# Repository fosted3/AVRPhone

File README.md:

AVRPhone
========

AVRPhone is an attempt to simplify and condense classic phone functionality while keeping modern security and openness in mind. The project aims to use a combination of easily accessible off-the-shelf hardware and clear and modular open source software in pursuit of this goal.

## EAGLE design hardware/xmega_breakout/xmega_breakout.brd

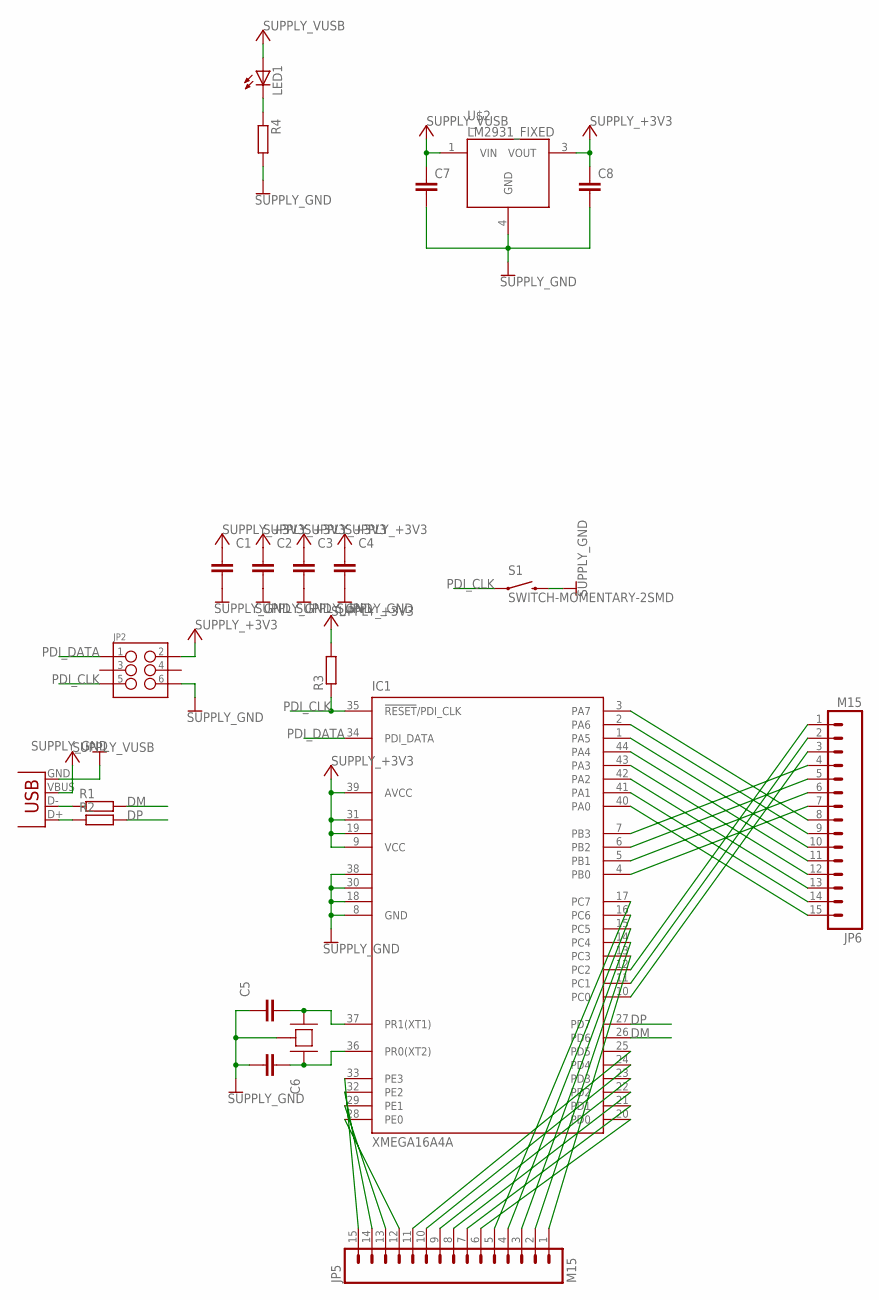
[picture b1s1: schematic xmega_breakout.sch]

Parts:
C1, C2, C3, C4, C5, C6: CAPACITOR_NPOL-0402; C402
C7, C8: C-EUC1210; C1210
IC1: XMEGA16A4A; TQFP44
JP1: USBSMD; USB-MINIB
JP2: M03X22X3_SILK_SM; 2X3
JP5, JP6: M15; 1X15
LED1: LED-0603; LED-603
R1, R2, R3: RESISTOR-0402; R402
R4: RESISTOR-0603; R603
S1: SWITCH-MOMENTARY-2SMD; TACTILE_SWITCH_SMD
U$1: CRYSTAL-3.2X2.5; TSX-3225
U$2: LM2931_FIXED; DPAK

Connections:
+3V3: C1.1, C2.1, C3.1, C4.1, C8.1, IC1.9 (VCC), IC1.19 (VCC1), IC1.31 (VCC2), IC1.39 (AVCC), JP2.2, R3.2, U$2.3 (VOUT)
DM: IC1.26 (PD6), R1.2
DP: IC1.27 (PD7), R2.2
GND: C1.2, C2.2, C3.2, C4.2, C5.1, C6.2, C7.2, C8.2, IC1.8 (GND), IC1.18 (GND1), IC1.30 (GND2), IC1.38 (GND3), JP1.GND, JP2.6, R4.2, S1.3 (2), U$1.G1 (GND), U$1.G2 (GND), U$2.4 (GND)
unnamed: C5.2, IC1.37 (PR1(XT1)), U$1.C1
unnamed: C6.1, IC1.36 (PR0(XT2)), U$1.C2
unnamed: JP1.D-, R1.1
unnamed: JP1.D+, R2.1
unnamed: IC1.33 (PE3), JP5.15
unnamed: IC1.32 (PE2), JP5.14
unnamed: IC1.29 (PE1), JP5.13
unnamed: IC1.28 (PE0), JP5.12
unnamed: IC1.25 (PD5), JP5.11
unnamed: IC1.24 (PD4), JP5.10
unnamed: IC1.23 (PD3), JP5.9
unnamed: IC1.22 (PD2), JP5.8
unnamed: IC1.21 (PD1), JP5.7
unnamed: IC1.20 (PD0), JP5.6
unnamed: IC1.17 (PC7), JP5.5
unnamed: IC1.16 (PC6), JP5.4
unnamed: IC1.15 (PC5), JP5.3
unnamed: IC1.14 (PC4), JP5.2
unnamed: IC1.13 (PC3), JP5.1
unnamed: IC1.12 (PC2), JP6.1
unnamed: IC1.11 (PC1), JP6.2
unnamed: IC1.10 (PC0), JP6.3
unnamed: IC1.7 (PB3), JP6.4
unnamed: IC1.6 (PB2), JP6.5
unnamed: IC1.5 (PB1), JP6.6
unnamed: IC1.4 (PB0), JP6.7
unnamed: IC1.3 (PA7), JP6.8
unnamed: IC1.2 (PA6), JP6.9
unnamed: IC1.1 (PA5), JP6.10
unnamed: IC1.44 (PA4), JP6.11
unnamed: IC1.43 (PA3), JP6.12
unnamed: IC1.42 (PA2), JP6.13
unnamed: IC1.41 (PA1), JP6.14
unnamed: IC1.40 (PA0), JP6.15
unnamed: LED1.C, R4.1
PDI_CLK: IC1.35 (!RESET!/PDI_CLK), JP2.5, R3.1, S1.1
PDI_DATA: IC1.34 (PDI_DATA), JP2.1
VUSB: C7.1, JP1.VBUS, LED1.A, U$2.1 (VIN)

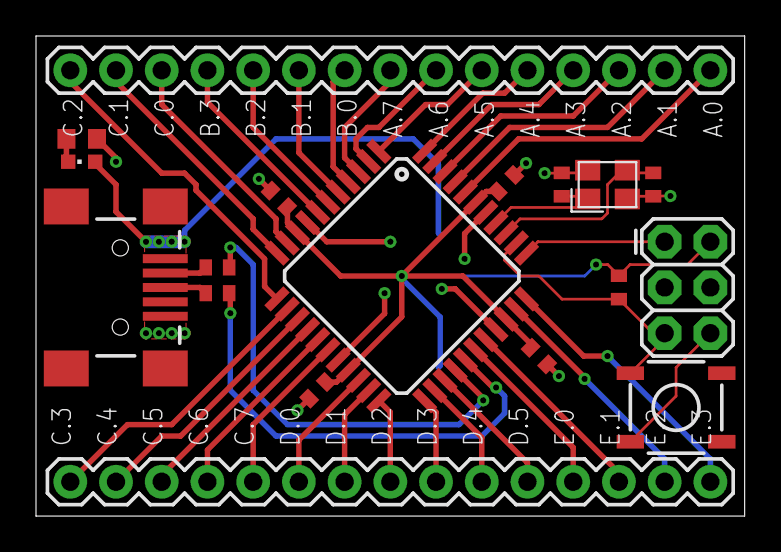
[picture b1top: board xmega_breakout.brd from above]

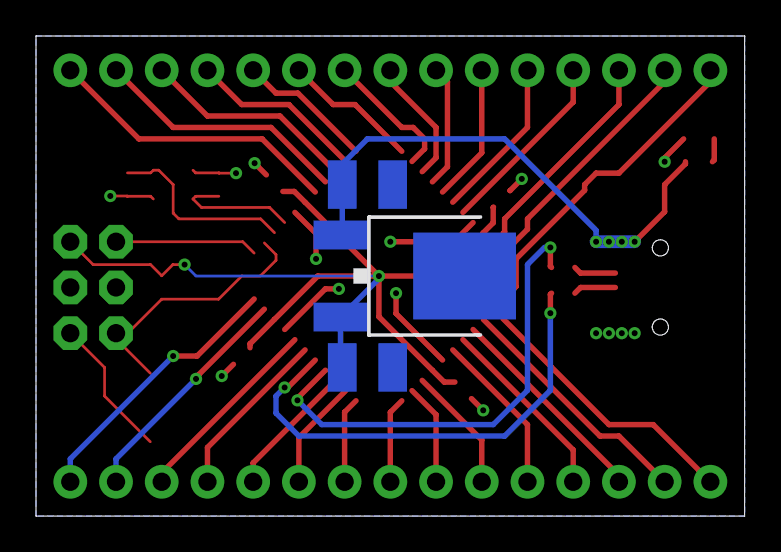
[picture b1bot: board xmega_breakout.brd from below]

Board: 2 copper layers, 39.4 x 26.7 mm, 21 parts (3 on the bottom side), 42 nets.

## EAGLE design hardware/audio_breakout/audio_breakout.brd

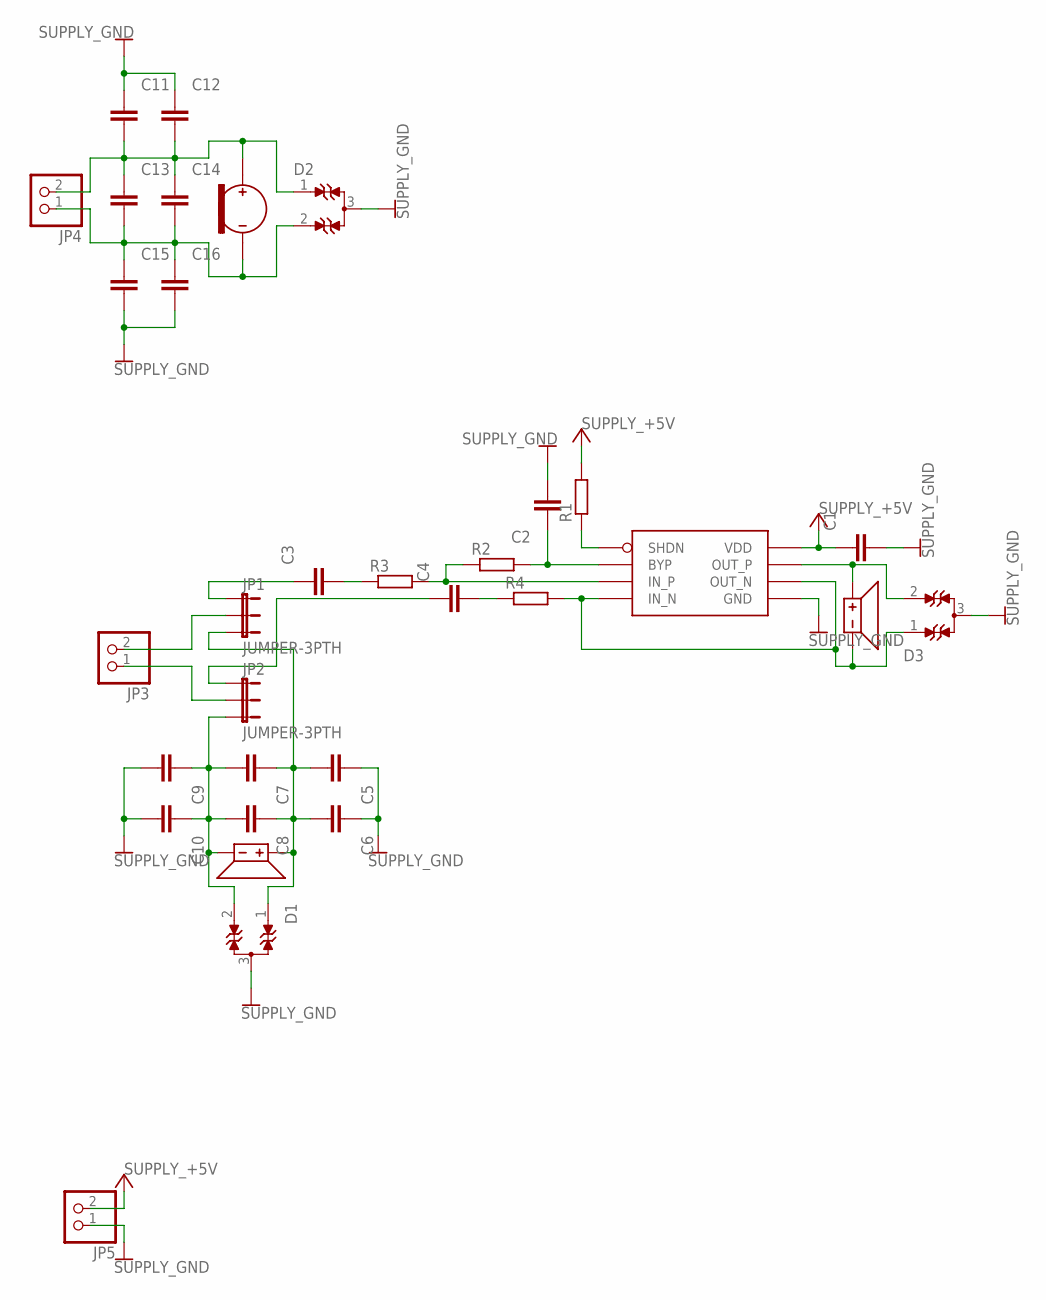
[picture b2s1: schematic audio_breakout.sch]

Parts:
C1, C2, C3, C4, C5, C6, C7, C8, C9, C10, C11, C12, C13, C14, C15, C16: CAPACITOR_NPOL-0603; C603
D1, D2, D3: WE-TVS_824022; WE-TVS_SOT23-3L
JP1, JP2: JUMPER-3PTH; 1X03
JP3, JP4, JP5: PINHD-1X2; 1X02
R1, R2, R3, R4: RESISTOR-0603; R603
U$1: LM4890; SOIC-8-NARROW
U$2: SPEAKER-2403-260-00001; 2403-260-00001
U$3: SPEAKER-2403-260-00031; 2403-260-00031
U$4: MIC-ELECTRET-9.7MM; 9.7MM-ELECTRET

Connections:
+5V: C1.1, JP5.2, R1.2, U$1.6 (VDD)
GND: C1.2, C2.2, C5.1, C6.1, C9.2, C10.2, C11.1, C12.1, C15.2, C16.2, D1.3 (GND), D2.3 (GND), D3.3 (GND), JP5.1, U$1.7 (GND)
unnamed: R1.1, U$1.1 (SHDN)
unnamed: C2.1, R2.2, U$1.2 (BYP)
unnamed: R2.1, R3.2, U$1.3 (IN_P)
unnamed: D3.1, R4.2, U$1.4 (IN_N), U$1.5 (OUT_N), U$2.-
unnamed: D3.2, U$1.8 (OUT_P), U$2.+
unnamed: C3.2, R3.1
unnamed: C4.2, R4.1
unnamed: C5.2, C6.2, C7.1, C8.1, D1.1, JP1.3, U$3.+
unnamed: C3.1, JP1.1
unnamed: C4.1, JP2.1
unnamed: C7.2, C8.2, C9.1, C10.1, D1.2, JP2.3, U$3.-
unnamed: JP1.2, JP3.2
unnamed: JP2.2, JP3.1
unnamed: C11.2, C12.2, C13.1, C14.1, D2.1, JP4.2, U$4.+
unnamed: C13.2, C14.2, C15.1, C16.1, D2.2, JP4.1, U$4.-

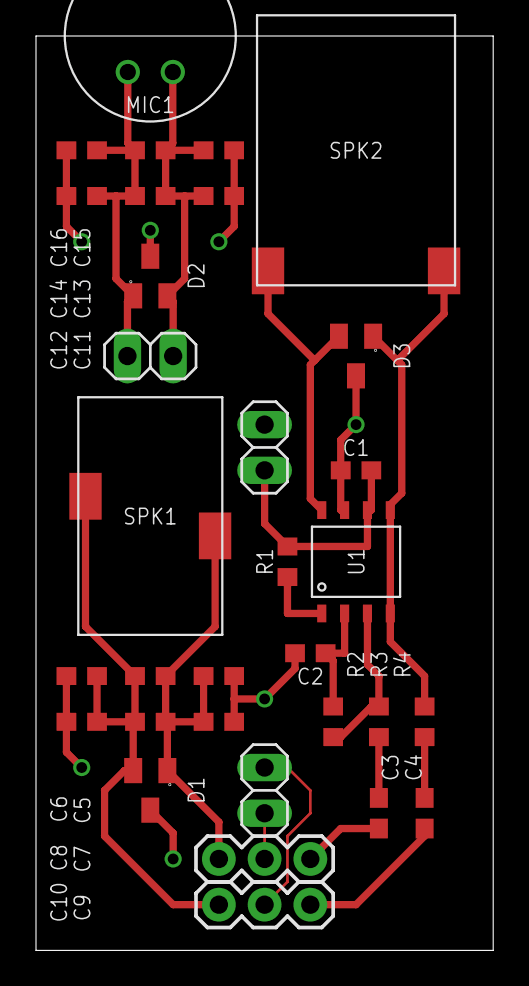
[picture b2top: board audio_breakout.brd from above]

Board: 2 copper layers, 25.4 x 50.8 mm, 33 parts (1 on the bottom side), 17 nets.

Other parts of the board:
U$6: OSHW-LOGO-L

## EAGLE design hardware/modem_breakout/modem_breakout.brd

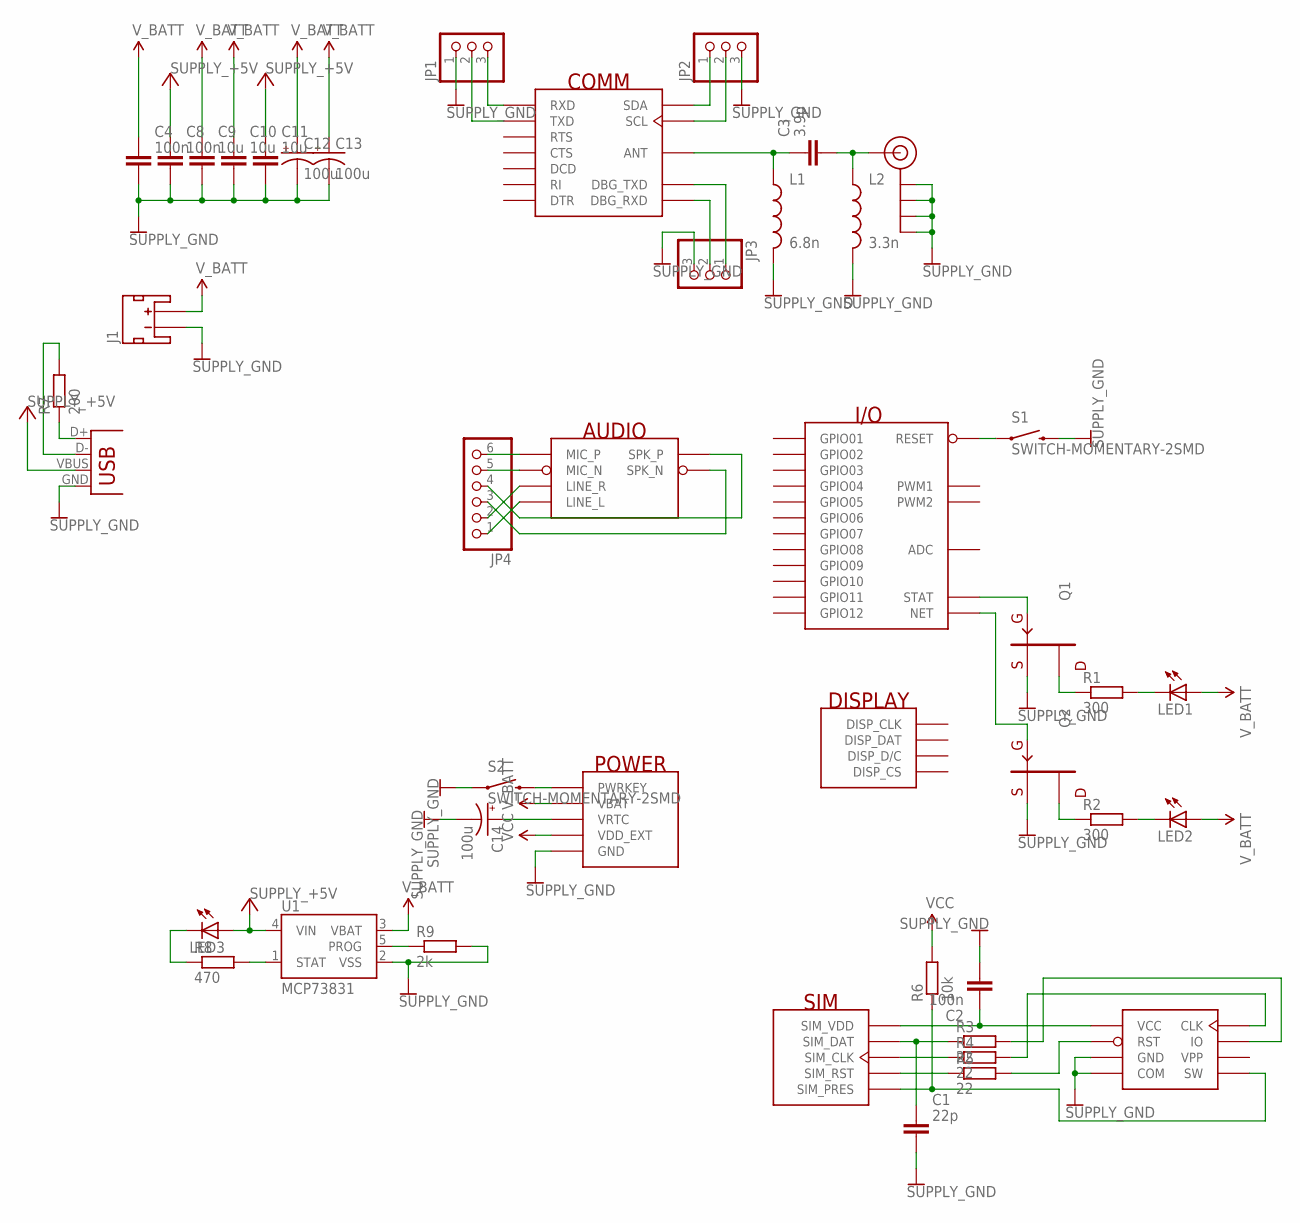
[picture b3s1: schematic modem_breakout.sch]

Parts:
C1: 22p; C402
C2, C4, C8: 100n; C402
C3: 3.9p; C603
C9, C10, C11: 10u; C805
C12, C13, C14: 100u; EIA3528
J1: JST_2MM_MALE; JST-2-SMD
J$1: SMA_EDGE; SMA-EDGE
JP1, JP2, JP3: PINHD-1X3; 1X03
JP4: PINHD-1X6; 1X06
JP5: USB-SMD-NS; USB-MINIB-NOSTOP
L1: 6.8n; 0603
L2: 3.3n; 0603
LED1, LED2, LED3: LED-0603; LED-603
Q1, Q2: TRANSISTOR_FET-N; SOT-23
R1, R2: 300; R603
R3, R4, R5: 22; R402
R6: 10k; R402
R7: 200; R603
R8: 470; R603
R9: 2k; R402
S1, S2: SWITCH-MOMENTARY-2SMD; TACTILE_SWITCH_SMD
U1: MCP73831; SOT23-5
U$1: SIM900
U$2: SIM-MICRO; 1041180811

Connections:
+5V: C8.1, C11.1, JP5.VBUS, LED3.A, U1.4 (VIN)
GND: C1.2, C2.2, C4.2, C8.2, C9.2, C10.2, C11.2, C12.C (-), C13.C (-), C14.C (-), J1.1 (-), J$1.GND@0 (GND), J$1.GND@1 (GND), J$1.GND@2 (GND), J$1.GND@3 (GND), JP1.1, JP2.3, JP3.3, JP5.GND, L1.2, L2.2, Q1.2 (S), Q2.2 (S), R9.2, S1.3 (2), S2.1, U1.2 (VSS), U$1.P$17 (GND), U$1.P$18 (GND), U$1.P$29 (GND), U$1.P$39 (GND), U$1.P$45 (GND), U$1.P$46 (GND), U$1.P$53 (GND), U$1.P$54 (GND), U$1.P$58 (GND), U$1.P$59 (GND), U$1.P$61 (GND), U$1.P$62 (GND), U$1.P$63 (GND), U$1.P$64 (GND), U$1.P$65 (GND), U$2.5 (GND), U$2.COMMON (COM), U$2.G1 (GND), U$2.G2 (GND), U$2.G3 (GND), U$2.G4 (GND), U$2.G5 (GND), U$2.G6 (GND)
unnamed: JP1.3, U$1.P$10 (RXD)
unnamed: JP1.2, U$1.P$9 (TXD)
unnamed: JP2.1, U$1.P$37 (SDA)
unnamed: JP2.2, U$1.P$38 (SCL)
unnamed: C3.1, L1.1, U$1.P$60 (ANT)
unnamed: JP3.1, U$1.P$27 (DBG_TXD)
unnamed: JP3.2, U$1.P$28 (DBG_RXD)
unnamed: C3.2, J$1.SIG (SIGNAL), L2.1
unnamed: C1.1, R3.1, U$1.P$31 (SIM_DAT)
unnamed: R6.1, U$1.P$34 (SIM_PRES), U$2.DETECT (SW)
unnamed: R4.1, U$1.P$32 (SIM_CLK)
unnamed: R5.1, U$1.P$33 (SIM_RST)
unnamed: C2.1, U$1.P$30 (SIM_VDD), U$2.1 (VCC)
unnamed: R3.2, U$2.7 (IO)
unnamed: R4.2, U$2.3 (CLK)
unnamed: R5.2, U$2.2 (RST)
unnamed: C14.A (+), U$1.P$26 (VRTC)
unnamed: Q1.1 (G), U$1.P$66 (STAT)
unnamed: Q2.1 (G), U$1.P$52 (NET)
unnamed: Q2.3 (D), R2.1
unnamed: Q1.3 (D), R1.1
unnamed: LED1.C, R1.2
unnamed: LED2.C, R2.2
unnamed: S2.3 (2), U$1.P$1 (PWRKEY)
unnamed: S1.1, U$1.P$16 (RESET)
unnamed: JP4.2, U$1.P$23 (LINE_R)
unnamed: JP4.1, U$1.P$24 (LINE_L)
unnamed: JP4.4, U$1.P$21 (SPK_P)
unnamed: JP4.3, U$1.P$22 (SPK_N)
unnamed: JP4.5, U$1.P$20 (MIC_N)
unnamed: JP4.6, U$1.P$19 (MIC_P)
unnamed: JP5.D-, R7.2
unnamed: JP5.D+, R7.1
unnamed: LED3.C, R8.1
unnamed: R8.2, U1.1 (STAT)
unnamed: R9.1, U1.5 (PROG)
VCC: R6.2, U$1.P$15 (VDD_EXT)
V_BATT: C4.1, C9.1, C10.1, C12.A (+), C13.A (+), J1.2 (+), LED1.A, LED2.A, U1.3 (VBAT), U$1.P$55 (VBAT), U$1.P$56 (VBAT), U$1.P$57 (VBAT)

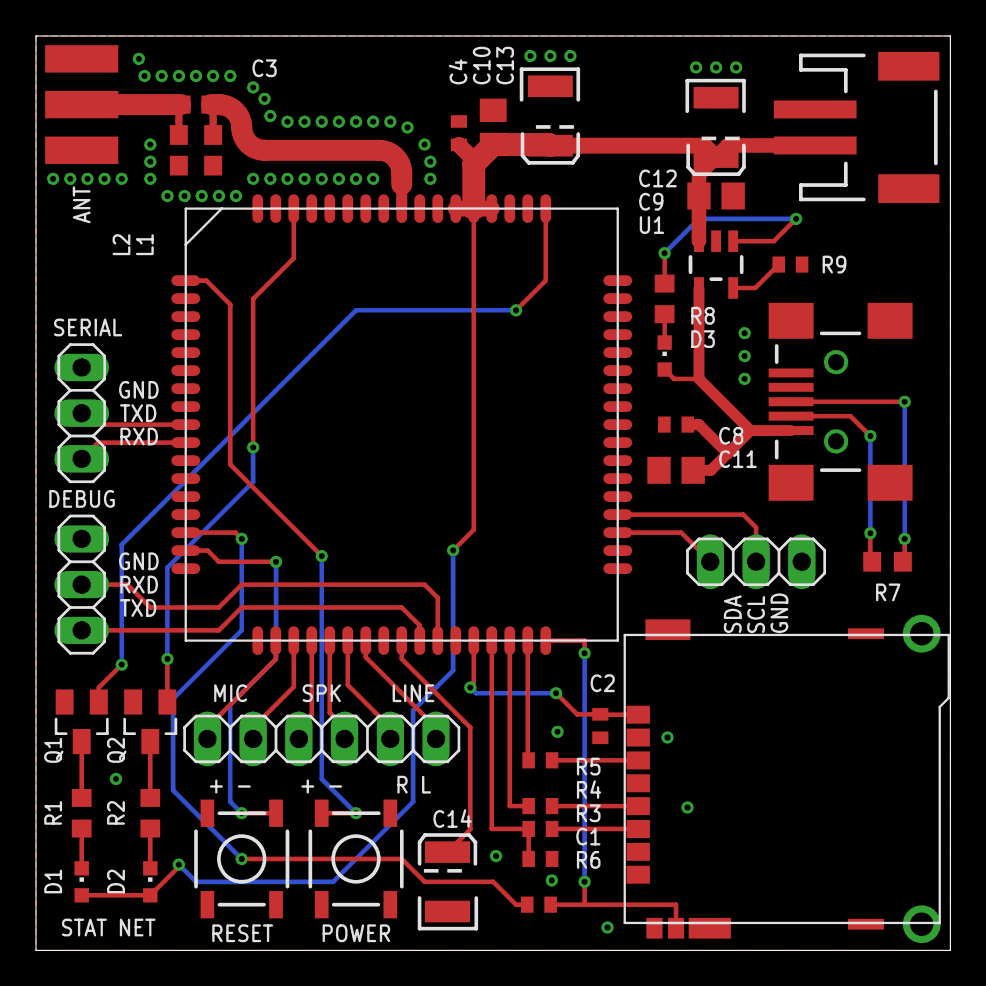
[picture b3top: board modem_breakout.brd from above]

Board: 2 copper layers, 50.8 x 50.8 mm, 40 parts (1 on the bottom side), 40 nets.

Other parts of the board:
U$3: OSHW-LOGO-L

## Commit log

2014-02-11 Added eagle files
2014-02-11 Changed .gitignore
2014-02-13 Changed .gitignore to reflect library additions, added a library to store parts created for the project
2014-02-14 Actually committed and updated .gitignore for EagleCAD
2014-02-15 Updated .gitignore with libraries
2014-02-15 Updated main module schematics
2014-02-28 added simple toolchain setup script
2014-02-28 Added xmega breakout test (blink) code/makefile
2014-03-02 fixed makefile to use more specific utilities, cleaned test
2014-03-18 added skeleton LCD code, instruction set for pcd8544
2014-03-29 Added silkscreening to breakout
2014-03-29 added image exports
2014-03-29 added lcd test files
2014-03-29 working lcd driver
2014-03-31 Notes on LCD/font interaction. Should be eventually handled below UI calls/interaction somehow
2014-04-01 added test partial lcd fill functionality
2014-04-02 fixed lcdUpdate bug
2014-04-04 lcdUpdateRange was terribly broken. removed, fixed update functions
2014-04-12 cleaner macro
2014-04-15 more macro modification
2014-04-15 initial sdcard things
2014-04-15 remove accidental .hex push
2014-04-15 fixed some stupid (typos)
2014-04-18 initial SD card initialization/communication added
2014-04-18 minor lcd upgrades/bugfix

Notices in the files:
parts and their libraries:
SparkFun-Passives: Licensing: CC v3.0 Share-Alike You are welcome to use this library for commercial purposes.
